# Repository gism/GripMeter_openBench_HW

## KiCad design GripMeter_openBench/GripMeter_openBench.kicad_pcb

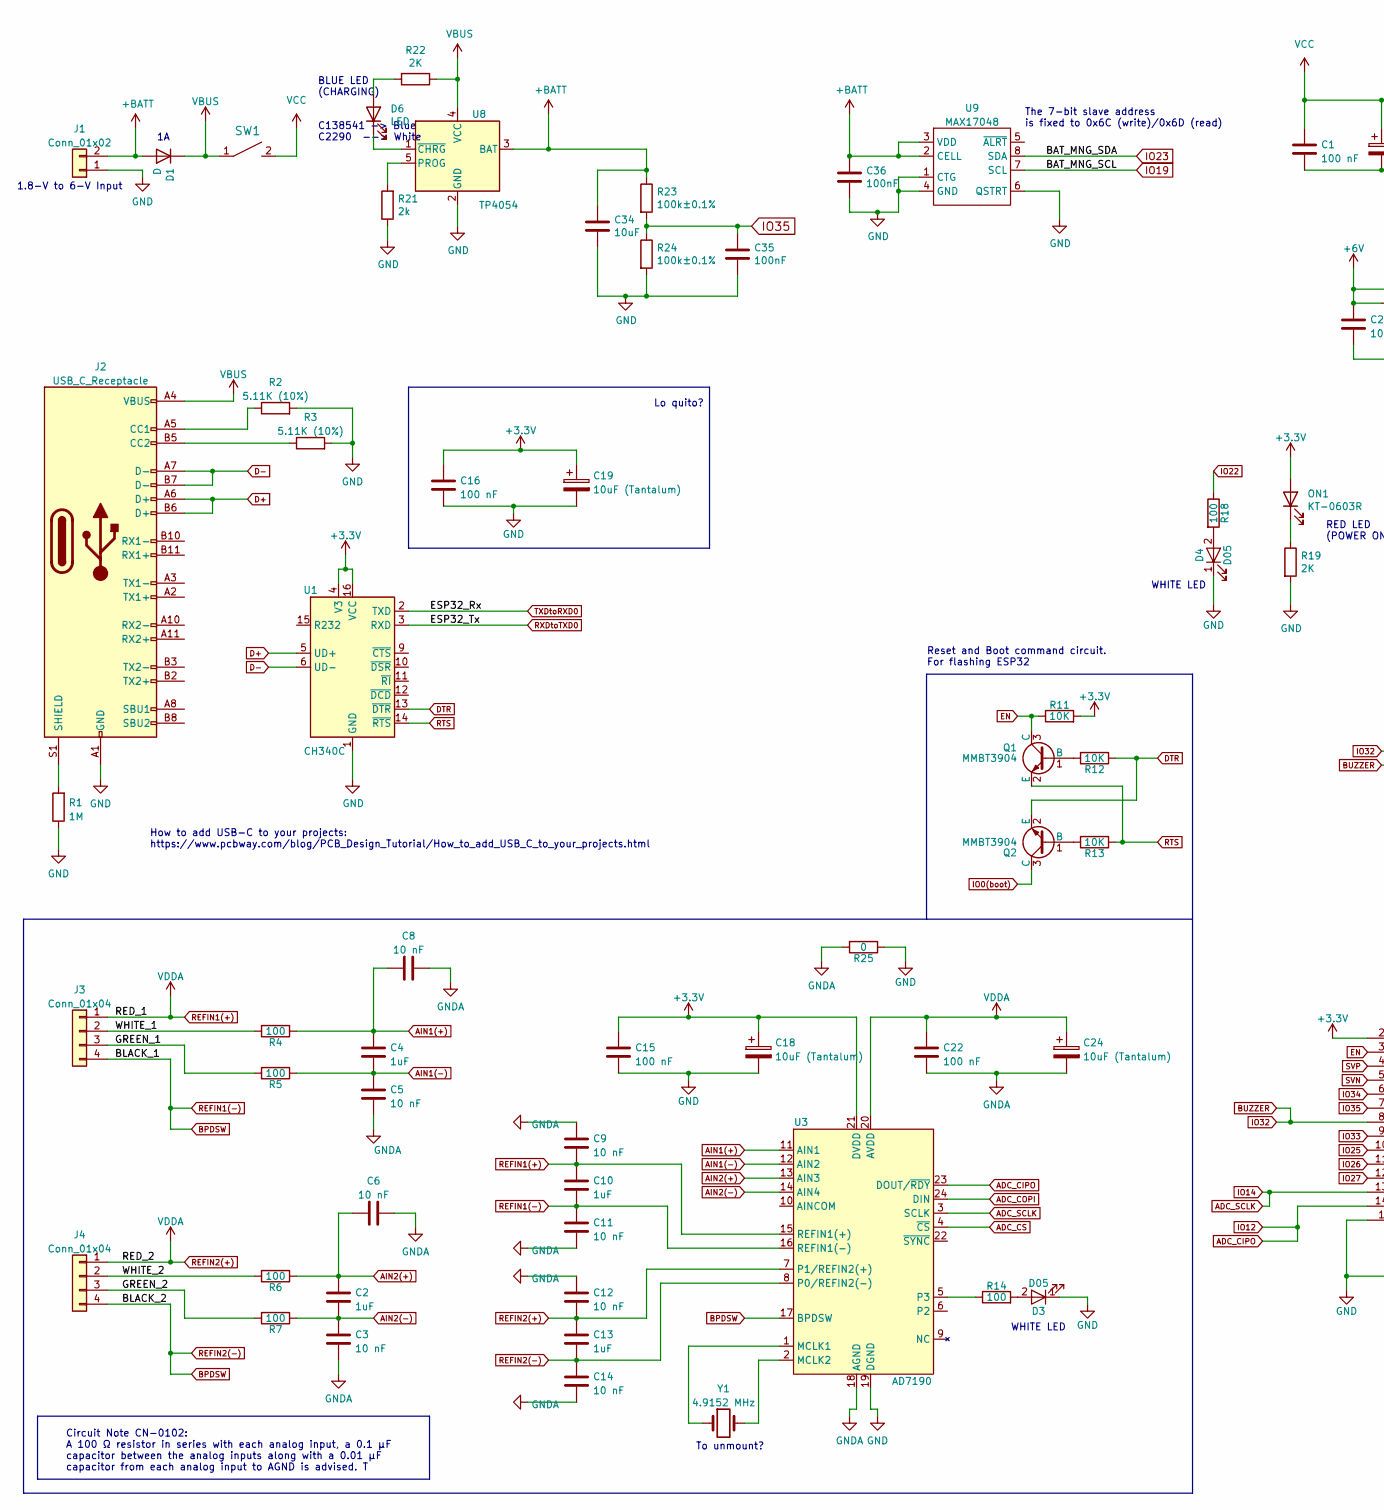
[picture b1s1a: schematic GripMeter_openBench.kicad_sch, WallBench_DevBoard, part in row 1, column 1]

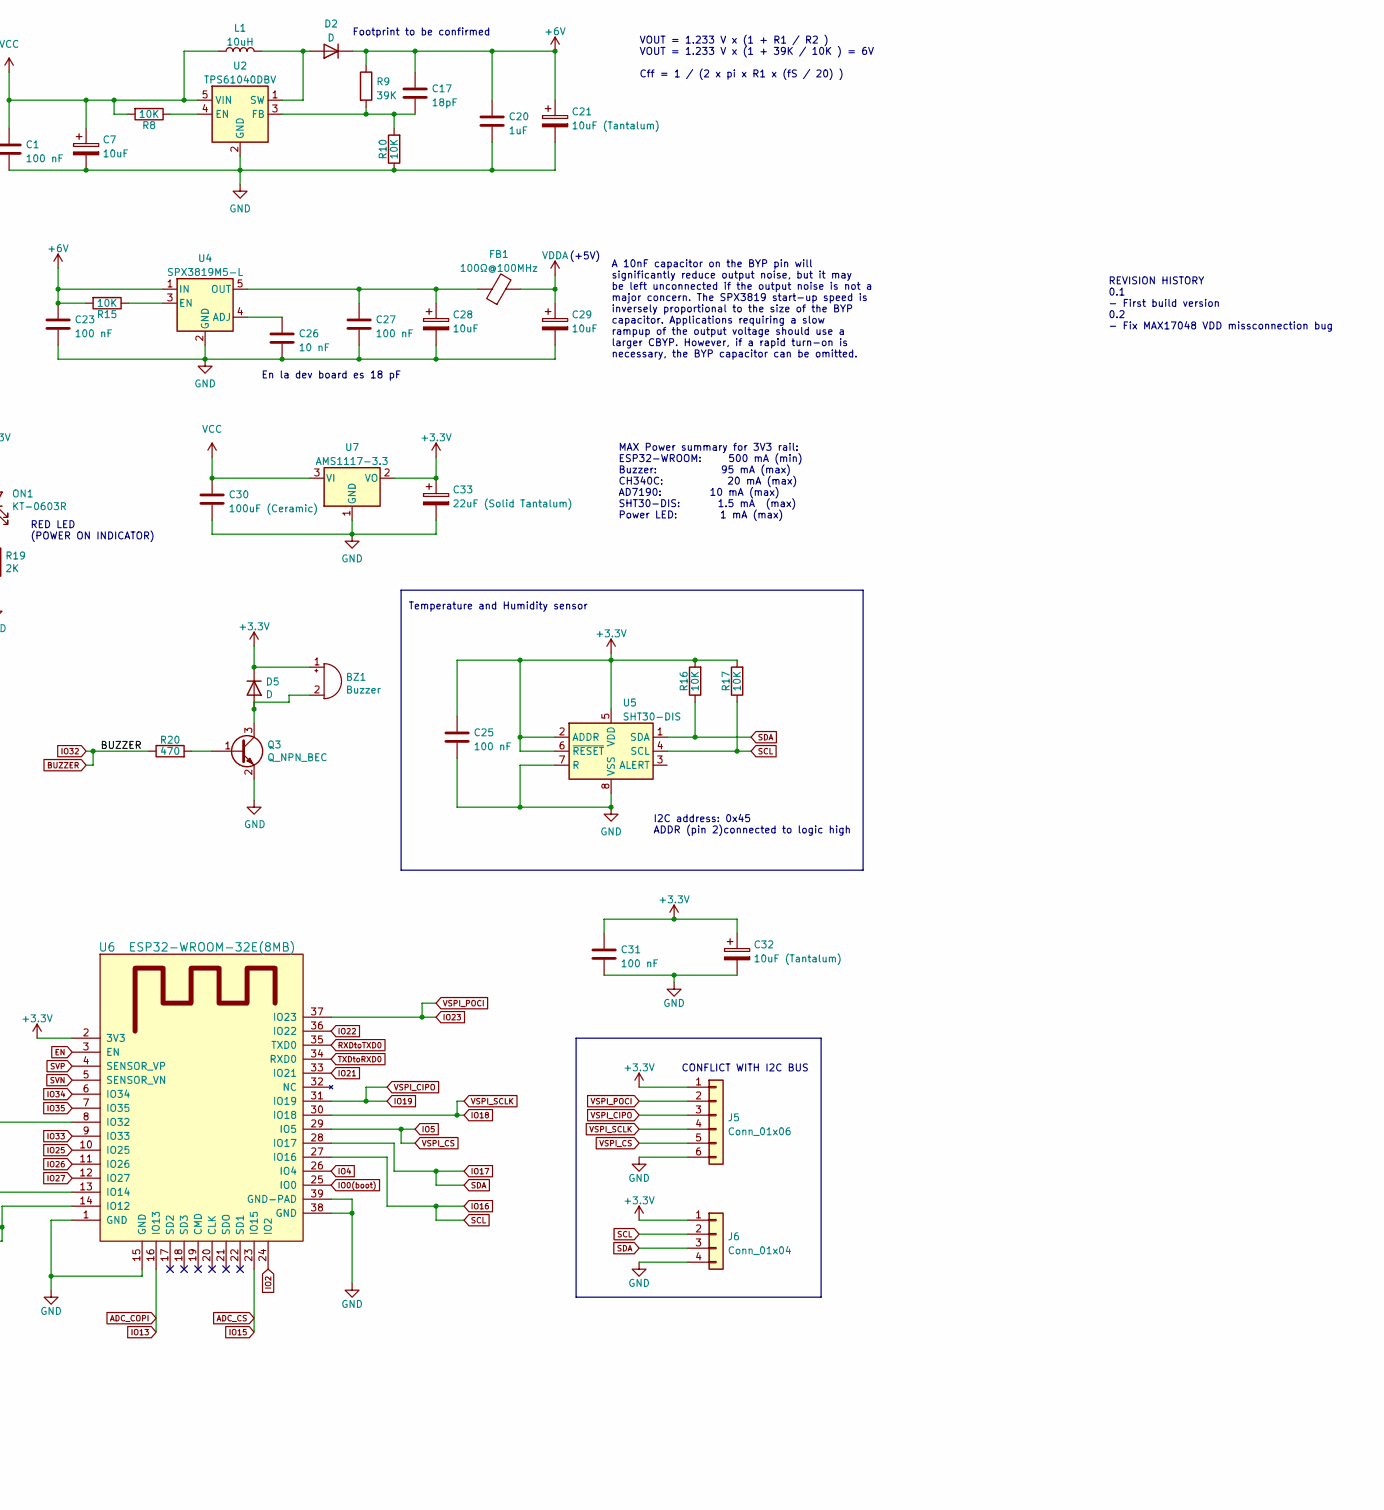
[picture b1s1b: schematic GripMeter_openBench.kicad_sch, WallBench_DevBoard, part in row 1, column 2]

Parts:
BZ1: Buzzer; PUIAudio_SMT_0825_S_4_R; MPN MLT-7525; LCSC C95299
C1, C15, C16, C22, C23, C25, C27, C31: 100 nF; C_0603_1608Metric; MPN CC0603KRX7R9BB104; LCSC C14663
C2, C4, C10, C13, C20: 1uF; C_0402_1005Metric; MPN CL05A105KA5NQNC; LCSC C52923
C3, C5, C6, C8, C9, C11, C12, C14, C26: 10 nF; C_0402_1005Metric; MPN CL05B103KB5NNNC; LCSC 0402
C7, C28, C29: 10uF; C_1206_3216Metric; MPN TAJA106K016RNJ; LCSC C7171
C17: 18pF; C_0402_1005Metric; MPN 0402CG180J500NT; LCSC C1549
C18, C19, C21, C24, C32: 10uF (Tantalum); C_1206_3216Metric; MPN TAJA106K016RNJ; LCSC C7171
C30: 100uF (Ceramic); C_1206_3216Metric; MPN CL31A107MQHNNNE; LCSC C15008
C33: 22uF (Solid Tantalum); C_1206_3216Metric; MPN TC212A226K010Y; LCSC C108526
C34: 10uF; C_0805_2012Metric; LCSC C440198
C35, C36: 100nF; C_0603_1608Metric; LCSC C14663
D1, D5: D; D_SOD-123F; MPN SM4007PL; LCSC C64898
D2: D; D_SMA; MPN SS14; LCSC C2480
D3, D4: D05; LED_0603_1608Metric; MPN C2290; LCSC C2290
D6: LED; LED_0603_1608Metric; LCSC C2290
FB1: 100Ω@100MHz; L_0805_2012Metric; MPN GZ2012D101TF; LCSC C1015
J1: Conn_01x02; JST_ZH_1x02P_1.5mm; MPN S2B-ZR-3.4(LF)(SN); LCSC C160729
J2: USB_C_Receptacle; USB_C_Receptacle_HRO_TYPE-C-31-M-12; MPN 918-418K2023S40001; LCSC C167321
J3, J4, J6: Conn_01x04; JST_ZH_1x04P_1.5mm; MPN S4B-ZR(LF)(SN); LCSC C157924
J5: Conn_01x06; JST_ZH_1x06P_1.5mm; MPN B6B-ZR(LF)(SN); LCSC C225150
L1: 10uH; L_0603_1608Metric; MPN SDFL1608S100KTF; LCSC C1035
ON1: KT-0603R; LED_0603_1608Metric; MPN KT-0603R; LCSC C2286
Q1, Q2: MMBT3904; SOT-23; MPN MMBT3904; LCSC C20526
Q3: Q_NPN_BEC; SOT-23; MPN MMBT3904; LCSC C20526
R1: 1M; R_0603_1608Metric; MPN 0603WAF1004T5E; LCSC C22935
R2, R3: 5.11K (10%); R_0603_1608Metric; MPN 0603WAF5111T5E; LCSC C23067
R4, R5, R6, R7, R14, R18: 100; R_0603_1608Metric; MPN 0603WAF1000T5E; LCSC C22775
R8, R10, R11, R12, R13, R15, R16, R17: 10K; R_0603_1608Metric; MPN 0603WAF1002T5E; LCSC C25804
R9: 39K; R_0402_1005Metric; MPN 0402WGF3902TCE; LCSC C25783
R19: 2K; R_0603_1608Metric; MPN 0603WAF2001T5E; LCSC C22975
R20: 470; R_0603_1608Metric; MPN 0603WAF4700T5E; LCSC C23179
R21: 2k; R_0603_1608Metric; LCSC C22975
R22: 2K; R_0603_1608Metric; LCSC C22975
R23, R24: 100k±0.1%; R_0603_1608Metric; LCSC C335088
R25: 0; R_0603_1608Metric; MPN 0603WAF0000T5E; LCSC C21189
SW1: SWITCH_SPST-esp32bb-rescue; C609826; MPN SK22D02L5; LCSC C609826
U1: CH340C; SOIC-16_3.9x9.9mm_P1.27mm; MPN CH340C; LCSC C84681
U2: TPS61040DBV; SOT-23-5; MPN TPS61040DBVR; LCSC C7722
U3: AD7190; TSSOP-24_4.4x7.8mm_P0.65mm; LCSC C19566
U4: SPX3819M5-L; SOT-23-5; MPN SPX3819M5-L-5-0/TR; LCSC C13417
U5: SHT30-DIS; Sensirion_DFN-8-1EP_2.5x2.5mm_P0.5mm_EP1.1x1.7mm; MPN SHT30-DIS-B10KS; LCSC C2687423
U6: ESP32-WROOM-32E(8MB); ESP32-WROOM; MPN ESP32-WROOM-32E(8MB); LCSC C701342
U7: AMS1117-3.3; SOT-223-3_TabPin2; MPN AMS1117-3.3V; LCSC C173386
U8: TP4054; TSOT-23-5; LCSC C32574
U9: MAX17048; TDFN-8-1EP_2x2mm_P0.5mm_EP0.8x1.2mm
Y1: 4.9152 MHz; Crystal_SMD_HC49-SD; MPN TXM4.9152M0002491LFBEO00T; LCSC C362350

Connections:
+3V3: BZ1.1 (-), C15.1, C16.1, C18.1, C19.1, C25.1, C31.1, C32.1, C33.1, D5.1 (K), J5.1, J6.1, ON1.2 (A), R11.2, R16.2, R17.2, U1.4 (V3), U1.16 (VCC), U3.21 (DVDD), U5.2 (ADDR), U5.5 (VDD), U5.6 (~RESET), U6.2 (3V3), U7.2 (VO)
+6V: C17.1, C20.1, C21.1, C23.1, D2.1 (K), R9.1, R15.2, U4.1 (IN)
+BATT: C34.1, C36.1, D1.2 (A), J1.2, R23.1, U8.3 (BAT), U9.2 (CELL), U9.3 (VDD)
/GREEN_1: J3.3, R5.2
/GREEN_2: J4.3, R7.2
/WHITE_1: J3.2, R4.2
/WHITE_2: J4.2, R6.2
ADC_CIPO: U3.23 (DOUT/~RDY), U6.14 (IO12)
ADC_COPI: U3.24 (DIN), U6.16 (IO13)
ADC_CS: U3.4 (~CS), U6.23 (IO15)
ADC_SCLK: U3.3 (SCLK), U6.13 (IO14)
AIN1(+): C4.1, C8.1, R4.1, U3.11 (AIN1)
AIN1(-): C4.2, C5.1, R5.1, U3.12 (AIN2)
AIN2(+): C2.1, C6.1, R6.1, U3.13 (AIN3)
AIN2(-): C2.2, C3.2, R7.1, U3.14 (AIN4)
BPDSW: C10.2, C11.1, C13.2, C14.1, J3.4, J4.4, U3.8 (P0/REFIN2(-)), U3.16 (REFIN1(-)), U3.17 (BPDSW)
BUZZER: R20.1, U6.8 (IO32)
D+: J2.A6 (D+), J2.B6 (D+), U1.5 (UD+)
D-: J2.A7 (D-), J2.B7 (D-), U1.6 (UD-)
DTR: Q2.2 (E), R12.1, U1.13 (~DTR)
EN: Q1.3 (C), R11.1, U6.3 (EN)
GND: C1.2, C7.2, C15.2, C16.2, C18.2, C19.2, C20.2, C21.2, C23.2, C25.2, C26.1, C27.2, C28.2, C29.2, C30.2, C31.2, C32.2, C33.2, C34.2, C35.2, C36.2, D3.1 (K), D4.1 (K), J1.1, J2.A1 (GND), J2.A12 (GND), J2.B1 (GND), J2.B12 (GND), J5.6, J6.4, Q3.2 (E), R1.1, R2.2, R3.2, R10.1, R19.2, R21.1, R24.2, R25.1, U1.1 (GND), U2.2 (GND), U3.19 (DGND), U4.2 (GND), U5.7 (R), U5.8 (VSS), U5.9 (VSS), U6.1 (GND), U6.15 (GND), U6.38 (GND), U6.39 (GND-PAD), U7.1 (GND), U8.2 (GND), U9.1 (CTG), U9.4 (GND), U9.6 (QSTRT)
GNDA: C3.1, C5.2, C6.2, C8.2, C9.1, C11.2, C12.1, C14.2, C22.2, C24.2, R25.2, U3.18 (AGND)
IO0(boot): Q2.3 (C), U6.25 (IO0)
IO2: U6.24 (IO2)
IO4: U6.26 (IO4)
IO5: J5.5, U6.29 (IO5)
IO16: J6.2, R17.1, U5.4 (SCL), U6.27 (IO16)
IO17: J6.3, R16.1, U5.1 (SDA), U6.28 (IO17)
IO18: J5.4, U6.30 (IO18)
IO19: J5.3, U6.31 (IO19), U9.7 (SCL)
IO21: U6.33 (IO21)
IO22: R18.1, U6.36 (IO22)
IO23: J5.2, U6.37 (IO23), U9.8 (SDA)
IO25: U6.10 (IO25)
IO26: U6.11 (IO26)
IO27: U6.12 (IO27)
IO33: U6.9 (IO33)
IO34: U6.6 (IO34)
IO35: C35.1, R23.2, R24.1, U6.7 (IO35)
unnamed: BZ1.2 (+), D5.2 (A), Q3.3 (C)
unnamed: D2.2 (A), L1.2, U2.1 (SW)
unnamed: D3.2 (A), R14.2
unnamed: D4.2 (A), R18.2
unnamed: D6.2 (A), R22.2
unnamed: D6.1 (K), U8.1 (~CHRG)
unnamed: J2.A5 (CC1), R2.1
unnamed: J2.B5 (CC2), R3.1
unnamed: J2.S1 (SHIELD), R1.2
unnamed: ON1.1 (K), R19.1
unnamed: Q1.1 (B), R12.2
unnamed: Q2.1 (B), R13.2
unnamed: Q3.1 (B), R20.2
unnamed: R8.1, U2.4 (EN)
unnamed: C17.2, R9.2, R10.2, U2.3 (FB)
unnamed: U3.1 (MCLK1), Y1.1
unnamed: U3.2 (MCLK2), Y1.2
unnamed: R14.1, U3.5 (P3)
unnamed: C26.2, U4.4 (ADJ)
unnamed: R15.1, U4.3 (EN)
unnamed: C27.1, C28.1, FB1.1, U4.5 (OUT)
unnamed: R21.2, U8.5 (PROG)
REFIN1(+): C9.2, C10.1, C12.2, C13.1, C22.1, C24.1, C29.1, FB1.2, J3.1, J4.1, U3.7 (P1/REFIN2(+)), U3.15 (REFIN1(+)), U3.20 (AVDD)
RTS: Q1.2 (E), R13.1, U1.14 (~RTS)
RXDtoTXD0: U1.3 (RXD), U6.35 (TXD0)
SVN: U6.5 (SENSOR_VN)
SVP: U6.4 (SENSOR_VP)
TXDtoRXD0: U1.2 (TXD), U6.34 (RXD0)
VBUS: D1.1 (K), J2.A4 (VBUS), J2.A9 (VBUS), J2.B4 (VBUS), J2.B9 (VBUS), R22.1, SW1.1, U8.4 (VCC)
VCC: C1.1, C7.1, C30.1, L1.1, R8.2, SW1.2, U2.5 (VIN), U7.3 (VI)

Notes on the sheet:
BLUE LED (CHARGING) C138541 -> Blue C2290 --> White
REVISION HISTORY 0.1 - First build version 0.2 - Fix MAX17048 VDD missconnection bug
Temperature and Humidity sensor
Reset and Boot command circuit. For flashing ESP32
(+5V)
How to add USB-C to your projects: https://www.pcbway.com/blog/PCB_Design_Tutorial/How_to_add_USB_C_to_your_projects.html
MAX Power summary for 3V3 rail: ESP32-WROOM: 500 mA (min) Buzzer: 95 mA (max) CH340C: 20 mA (max) AD7190: 10 mA (max) SHT30-DIS: 1.5 mA (max) Power LED: 1 mA (max)
The 7-bit slave address is fixed to 0x6C (write)/0x6D (read)
WHITE LED
To unmount?
Circuit Note CN-0102: A 100 Ω resistor in series with each analog input, a 0.1 μF capacitor between the analog inputs along with a 0.01 μF capacitor from each analog input to AGND is advised. T
VOUT = 1.233 V x (1 + R1 / R2 ) VOUT = 1.233 V x (1 + 39K / 10K ) = 6V Cff = 1 / (2 x pi x R1 x (fS / 20) )
I2C address: 0x45 ADDR (pin 2)connected to logic high
RED LED (POWER ON INDICATOR)
En la dev board es 18 pF
Footprint to be confirmed
A 10nF capacitor on the BYP pin will significantly reduce output noise, but it may be left unconnected if the output noise is not a major concern. The SPX3819 start-up speed is inversely proportional to the size of the BYP capacitor. Applications requiring a slow rampup of the output voltage should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
CONFLICT WITH I2C BUS
1.8-V to 6-V Input
Lo quito?

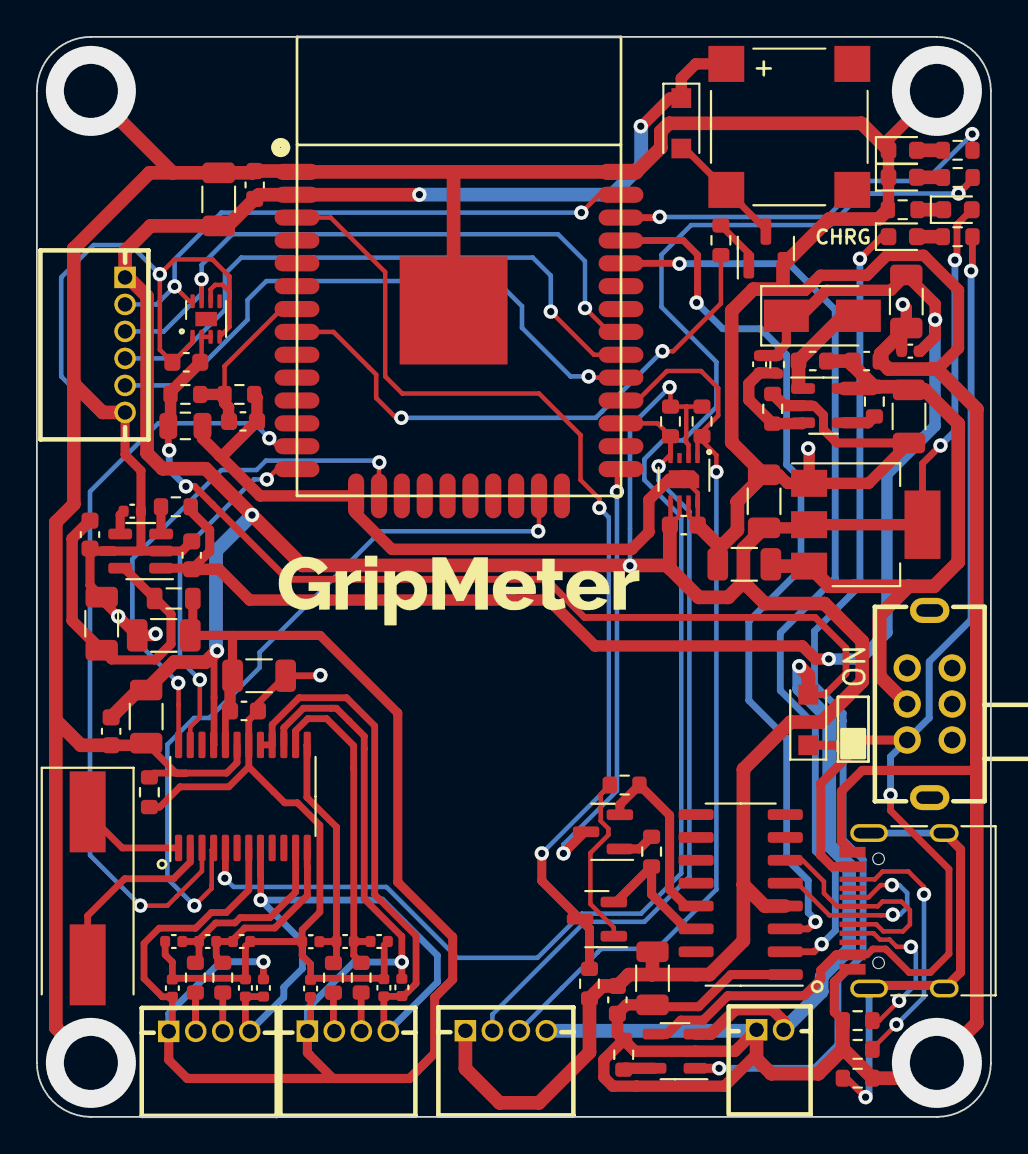
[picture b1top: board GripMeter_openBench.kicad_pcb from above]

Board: 2 copper layers, 53.0 x 60.0 mm, 91 parts (0 on the bottom side), 60 nets.

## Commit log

2022-08-13 Create LICENSE
2022-08-14 Draft
